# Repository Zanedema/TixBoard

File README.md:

# TixBoard - Digital Communications Education Board
### Schematic and idea derived from a [April 2022 thread from @m_ou_se on Twitter.](https://twitter.com/m_ou_se/status/1511091323612413965)

The TixBoard is a hands-on digital communications demonstration and education tool designed for everyone passionate about learning. From absolute beginners looking for a tactile introduction to how various flavors of digital communication function to experienced makers, educators, precocious cats, or bacteria looking for a unique perspective on the protocols that make our digital world tick.

## Operation

The TixBoard features a single RCA socket as its medium of communication. It utilizes inexpensive RCA cables and splitters to make arbitrary and easily reconfigurable networks of TixBoards, whether point to point or on a shared bus. On the board side, it features three switches that allow for the rapid and straightforward reconfiguration of any TixBoard. It is powered by two AA batteries, which should last a long time **provided that the output not be high during storage, as this will result in the LED running and draining the battery.** It is best to set the board to Hi-Z and disable the Pull-Up switch before storing your TixBoard. The onboard LED serves as a visual indicator of both the input recieved by the TixBoard in input mode, and the output of the TixBoard in output mode. The short circuit buzzer alerts the user when they have connected TixBoards in a way that will result in excessive battery drainage.

(picture here, lol)

### Input(Hi-Z)/Output Switch
The Input/Output switch is used to change the behavior of the TixBoard. The TixBoard can be configured to **Input(Hi-Z)**, where the TixBoard will act as an input, simply allowing the LED to flash with the input. Input(Hi-Z) can also be used as part of three-state logic so that when it is switched to Hi-Z[^1], it will effectively not influence the communication system. When switched to output, the behavior of the TixBoard is determined by the Low/High switch.

(picture here, lol)

### Low/High Switch
The **Low/High** switch determines whether the TixBoard outputs logical high or low. When set to high, the TixBoard will output logical high. When set to low, it will bring its output to ground. If two TixBoards are connected so that the logical high output of one is sunk directly into the logical low output of another, the short circuit buzzer will sound. Do not fear- your boards are not in peril. **Promptly reconfigure the circuit to prevent excessive battery drainage.**

(picture here, lol)

### Pull-Up Switch
The **Pull-Up** switch is used to make the output of the TixBoard default to logical high with the onboard 22kΩ pull-up resistor. A real-world example would be the I²C protocol, which grounds the output to produce a logical low, and toggles Hi-Z to let the pull-up resistor take the output to a higher voltage to make a logical high. An onboard capacitor will slow the transition from logical low to logical high to showcase one of this method's potential real-world downsides.

(picture here, lol)

[^1]: Fancy engineering speak for high impedance, a state where the output will let minimal current through. Think of it as a floating wire, as there is no path to ground. Quite literally, the Hi-Z/Input path is a dead end.

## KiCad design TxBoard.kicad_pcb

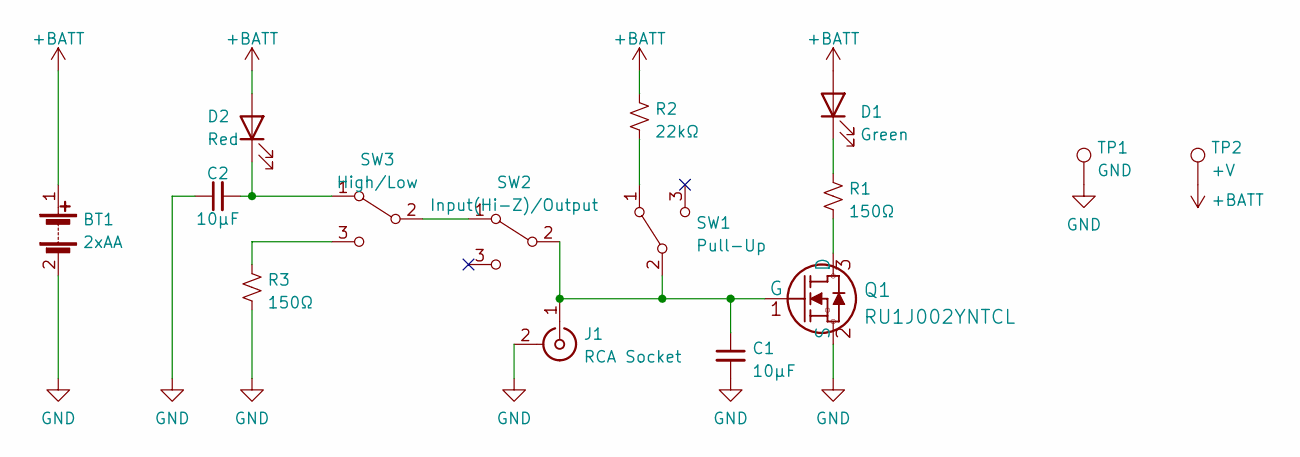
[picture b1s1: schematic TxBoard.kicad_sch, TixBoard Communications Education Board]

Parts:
BT1: 2xAA; BAT_BC2AAPC
C1, C2: 10μF; C_0805_2012Metric_Pad1.18x1.45mm_HandSolder
D1: Green; LED_0603_1608Metric_Pad1.05x0.95mm_HandSolder
D2: Red; LED_0603_1608Metric_Pad1.05x0.95mm_HandSolder
J1: RCA Socket; KLPX-0848A-2-B
Q1: RU1J002YNTCL; SOT-323_SC-70_Handsoldering
R1, R3: 150Ω; R_0603_1608Metric_Pad0.98x0.95mm_HandSolder
R2: 22kΩ; R_0603_1608Metric_Pad0.98x0.95mm_HandSolder
SW1: Pull-Up; JS102011SCQN
SW2: Input(Hi-Z)/Output; JS102011SCQN
SW3: High/Low; JS102011SCQN
TP1: GND; TestPoint_Pad_1.5x1.5mm
TP2: +V; TestPoint_Pad_1.5x1.5mm

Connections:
+BATT: BT1.1 (+), D1.2 (A), D2.2 (A), R2.1, TP2.1
GND: BT1.2 (-), C1.2, C2.1, J1.2 (Ext), Q1.2 (S), R3.1, TP1.1
unnamed: C1.1, J1.1 (In), Q1.1 (G), SW1.2 (B), SW2.2 (B)
unnamed: C2.2, D2.1 (K), SW3.1 (A)
unnamed: D1.1 (K), R1.1
unnamed: Q1.3 (D), R1.2
unnamed: R2.2, SW1.1 (A)
unnamed: R3.2, SW3.3 (C)
unnamed: SW2.1 (A), SW3.2 (B)

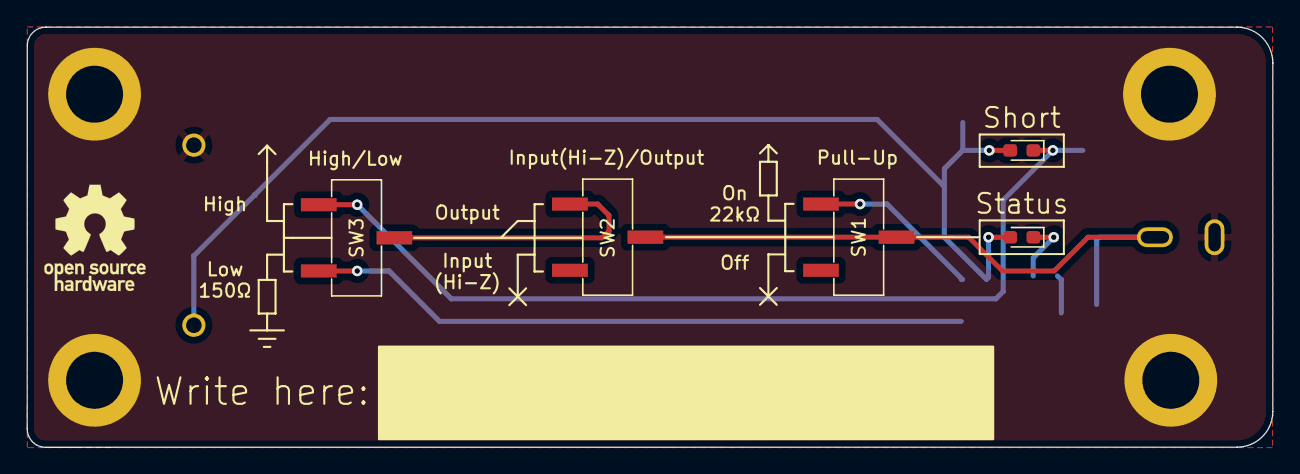
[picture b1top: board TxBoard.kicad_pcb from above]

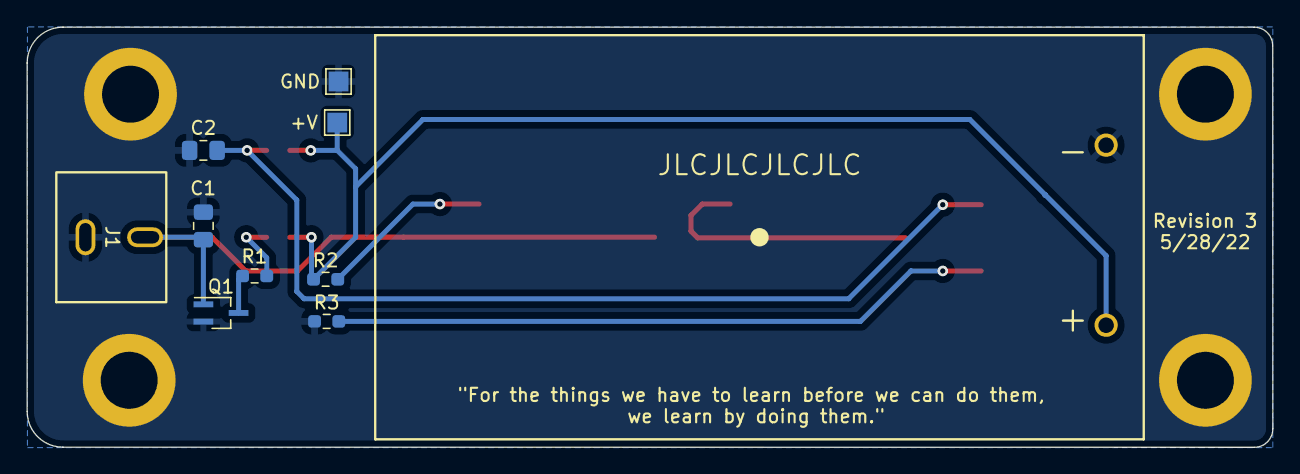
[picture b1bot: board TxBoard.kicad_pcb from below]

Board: 2 copper layers, 94.0 x 31.7 mm, 15 parts (10 on the bottom side), 9 nets.

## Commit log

2022-04-14 Initial
    Initial schematic + Datasheets
2022-04-15 Name Change
    Me, indecisive? Never.
2022-04-15 Details
    yay details
2022-04-15 I'm indecisive, okay???
    mo pictures, mo better-er
2022-04-16 Schematic (mostly) finished
    Removed libraries because I really rather not open that can of legal worms. Gonna have to find them yourself.
2022-04-16 Delete ul_RU1J002YNTCL/KiCAD/2022-04-14_18-46-42 directory
    oops
2022-04-16 oops pt 2
    lol
2022-04-17 Initial PCB
    First crack at PCB with silkscreen and layout. Added test points
2022-04-18 PCB Rev 2
    Todo: TixBoard text in mask. Logo imported too thin to clear DRC
2022-04-20 Prototype 1
    Board final review finished, DRC issues fixed (whoever made that RCA footprint needs to learn what the polygon tool does), production files generated and will be sent out for production soon. hope it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
2022-04-20 PDF
    a nice touch for easy github viewability
2022-04-21 Cost reduction
    dont wanna pay for no order number, so just put it where it is not visible
2022-05-05 Lessons learned
    >:(
2022-05-11 Design review 2
    good 4 prototype 2
2022-05-28 where was I
    oh yeah

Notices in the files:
TxBoard.kicad_sch:
[Designed with <3 in San Diego - Licensed under MIT License]
parts and their libraries:
Copyright 2021 Accelerated Designs. All rights reserved.
